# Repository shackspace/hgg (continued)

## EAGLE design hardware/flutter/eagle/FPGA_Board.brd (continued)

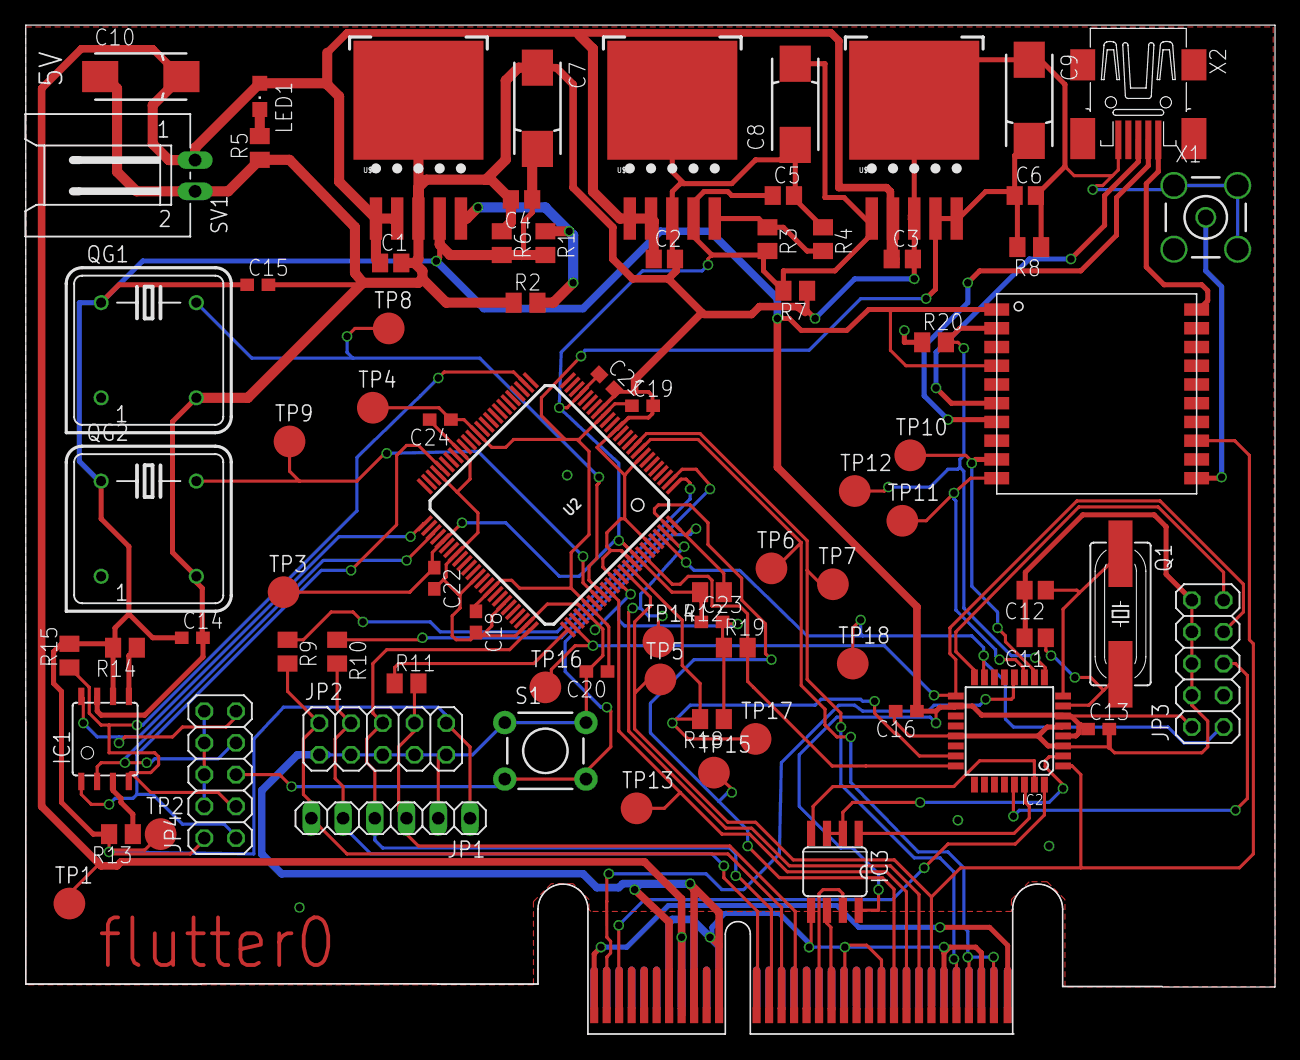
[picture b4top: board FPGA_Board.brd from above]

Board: 2 copper layers, 100.0 x 80.8 mm, 81 parts (0 on the bottom side), 53 nets.

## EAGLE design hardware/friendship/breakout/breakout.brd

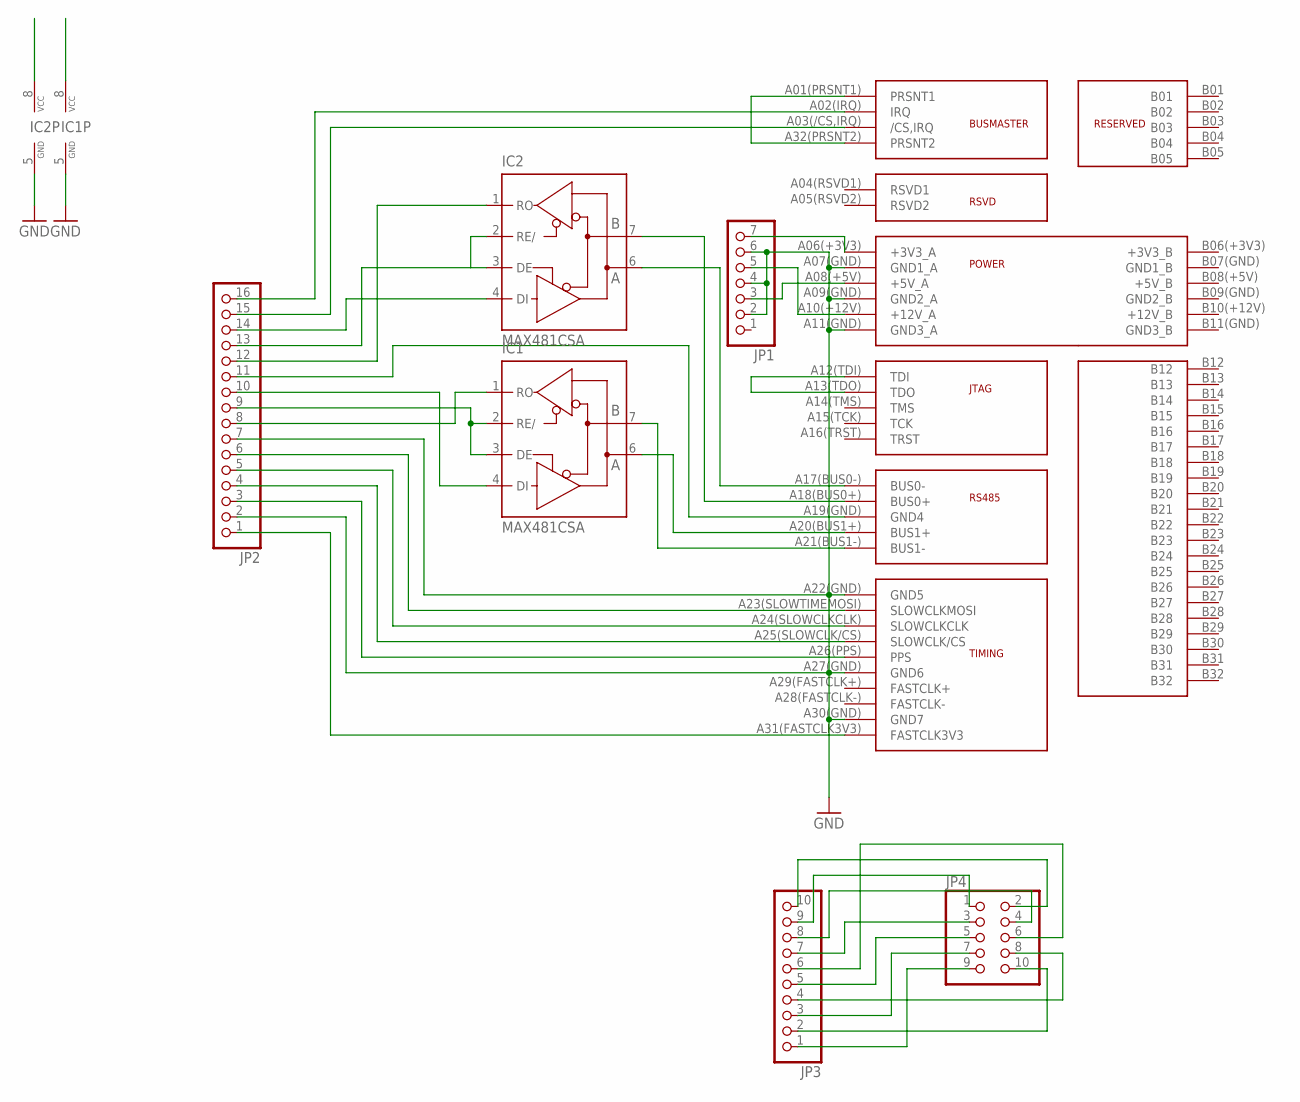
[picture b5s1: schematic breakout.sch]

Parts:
IC1, IC2: MAX481CSA; SO08
JP1: PINHD-1X7; 1X07
JP2: PINHD-1X16; 1X16
JP3: PINHD-1X10; 1X10
JP4: PINHD-2X5; 2X05
U$1: FRIENDSHIPCONNECTOR; FRIENDSHIP_EDGE_CONNECTOR

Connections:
GND: IC1.5 (GND), IC2.5 (GND), JP1.2, JP1.4, JP1.6, JP2.2, JP2.7, U$1.A07(GND) (GND1_A), U$1.A09(GND) (GND2_A), U$1.A11(GND) (GND3_A), U$1.A22(GND) (GND5), U$1.A27(GND) (GND6), U$1.A30(GND) (GND7)
unnamed: U$1.A01(PRSNT1) (PRSNT1), U$1.A32(PRSNT2) (PRSNT2)
unnamed: IC2.6 (A), U$1.A17(BUS0-) (BUS0-)
unnamed: IC2.7 (B), U$1.A18(BUS0+) (BUS0+)
unnamed: IC2.2 (RE/), IC2.3 (DE), JP2.13
unnamed: JP2.16, U$1.A02(IRQ) (IRQ)
unnamed: JP2.15, U$1.A03(/CS,IRQ) (/CS,IRQ)
unnamed: IC1.6 (A), U$1.A20(BUS1+) (BUS1+)
unnamed: IC2.4 (DI), JP2.14
unnamed: IC1.7 (B), U$1.A21(BUS1-) (BUS1-)
unnamed: JP2.11, U$1.A19(GND) (GND4)
unnamed: IC1.2 (RE/), IC1.3 (DE), JP2.9
unnamed: U$1.A12(TDI) (TDI), U$1.A13(TDO) (TDO)
unnamed: JP1.5, U$1.A10(+12V) (+12V_A)
unnamed: IC2.1 (RO), JP2.12
unnamed: IC1.1 (RO), JP2.8
unnamed: IC1.4 (DI), JP2.10
unnamed: JP2.6, U$1.A23(SLOWTIMEMOSI) (SLOWCLKMOSI)
unnamed: JP1.3, U$1.A08(+5V) (+5V_A)
unnamed: JP2.5, U$1.A24(SLOWCLKCLK) (SLOWCLKCLK)
unnamed: JP2.4, U$1.A25(SLOWCLK/CS) (SLOWCLK/CS)
unnamed: JP2.3, U$1.A26(PPS) (PPS)
unnamed: JP3.10, JP4.2
unnamed: JP2.1, U$1.A31(FASTCLK3V3) (FASTCLK3V3)
unnamed: JP3.9, JP4.1
unnamed: JP3.8, JP4.4
unnamed: JP3.7, JP4.3
unnamed: JP3.6, JP4.6
unnamed: JP3.5, JP4.5
unnamed: JP3.3, JP4.7
unnamed: JP3.4, JP4.8
unnamed: JP3.2, JP4.10
unnamed: JP3.1, JP4.9
VCC: IC1.8 (VCC), IC2.8 (VCC), JP1.7, U$1.A06(+3V3) (+3V3_A)

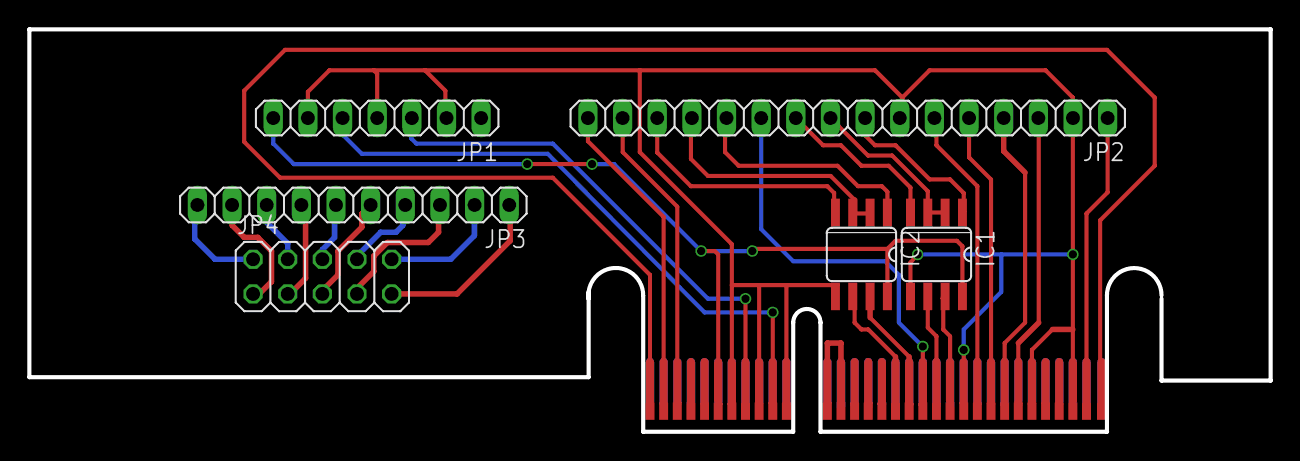
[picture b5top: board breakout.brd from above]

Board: 2 copper layers, 91.0 x 29.5 mm, 7 parts (0 on the bottom side), 34 nets.

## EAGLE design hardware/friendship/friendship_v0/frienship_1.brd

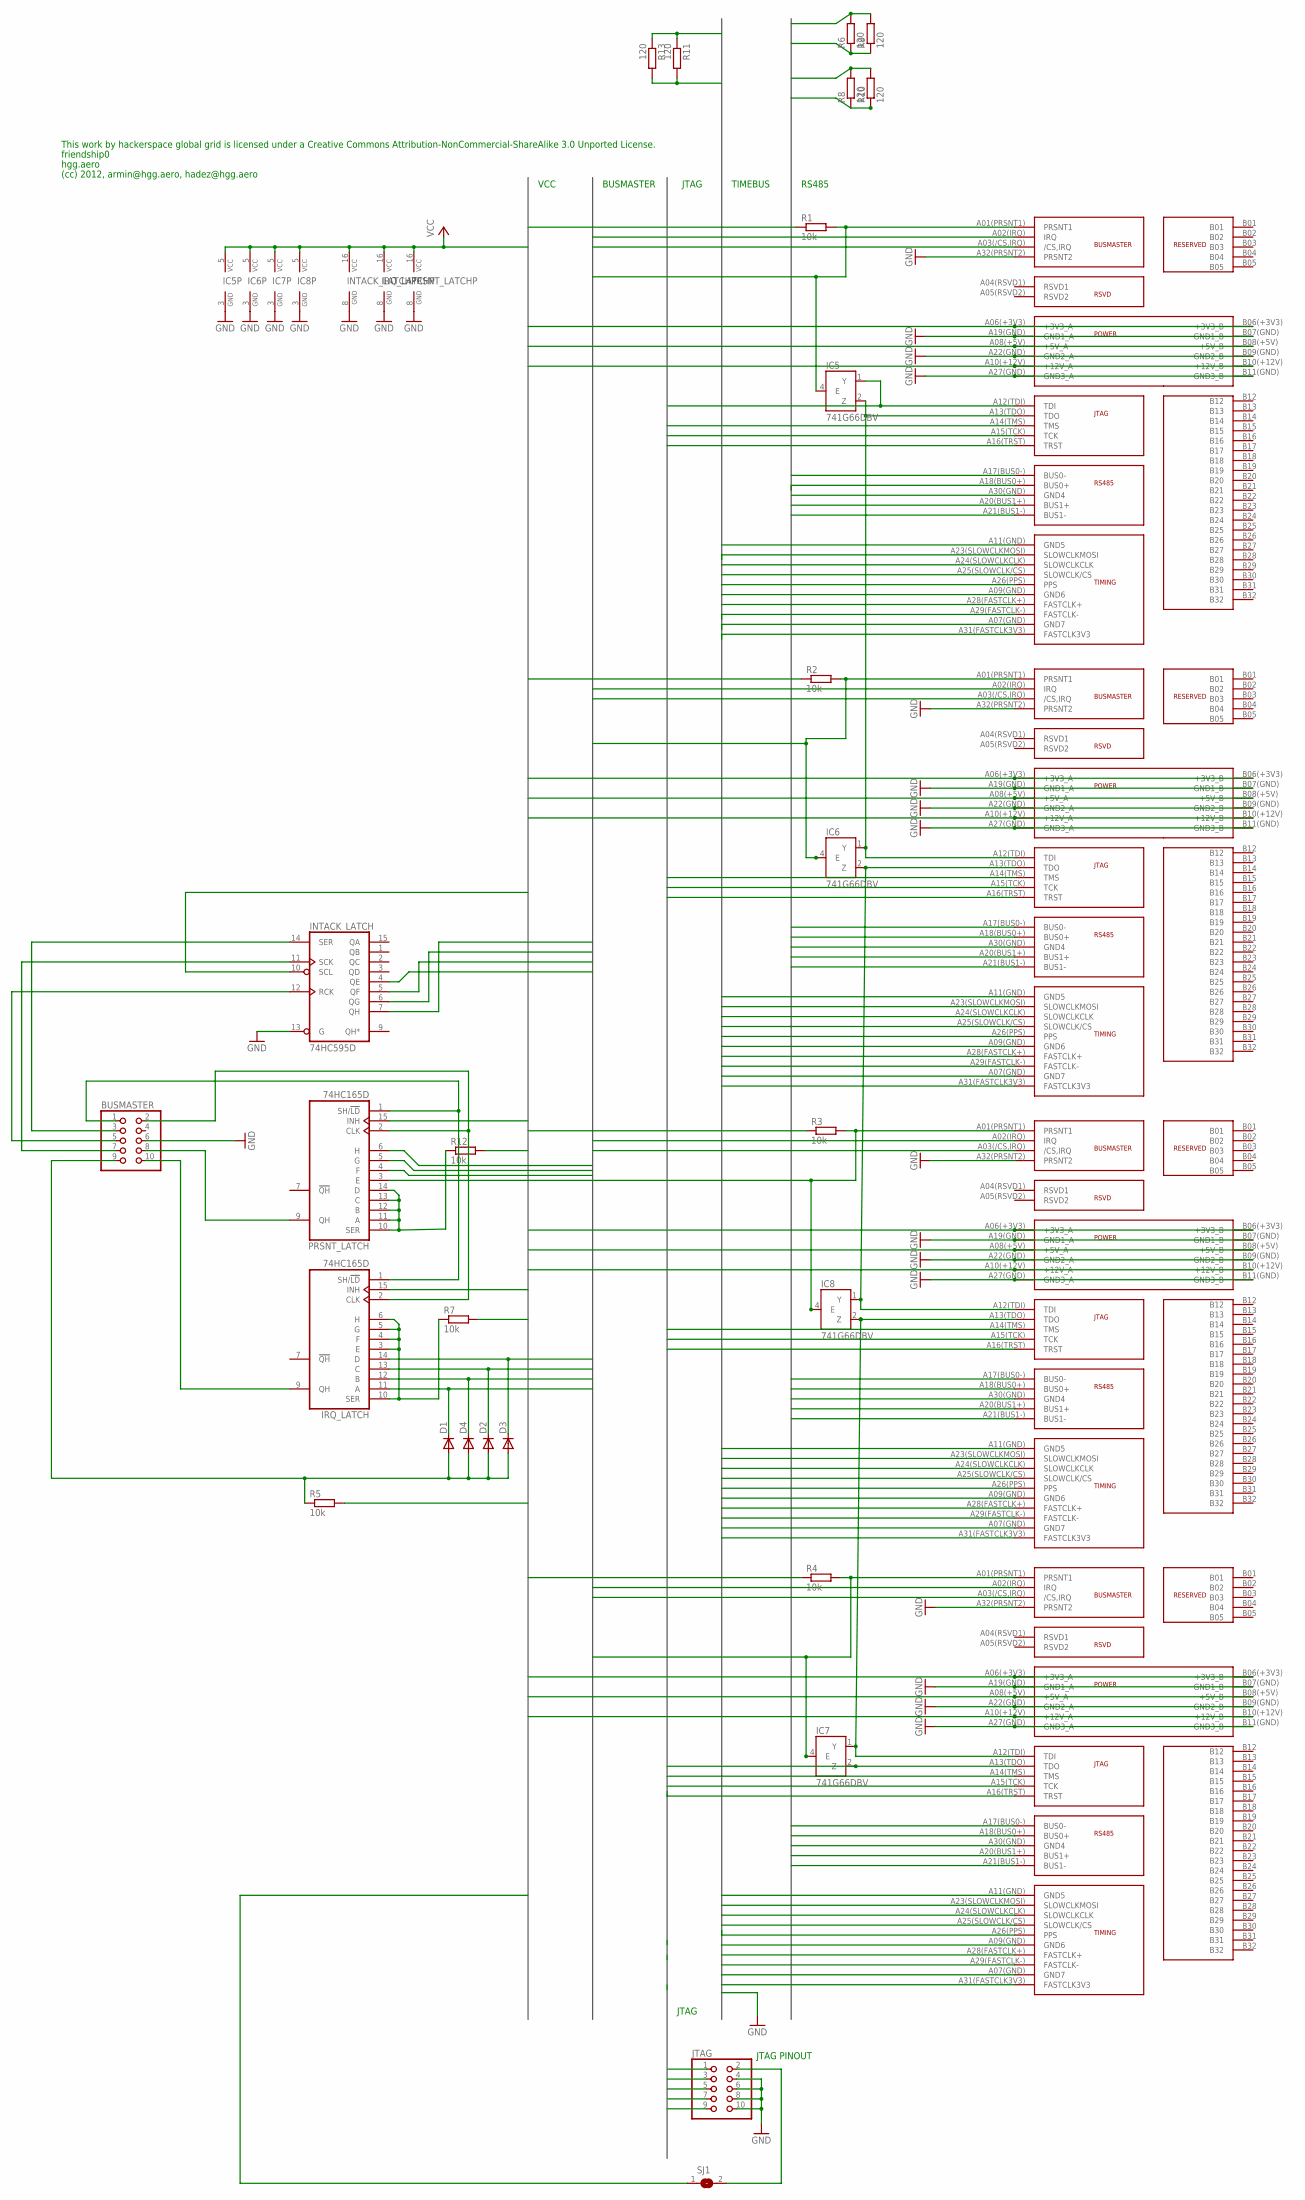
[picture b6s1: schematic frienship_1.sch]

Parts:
BUSMASTER: PINHD-2X5; 2X05
D1, D2, D3, D4: DIODE-SOD80C; SOD80C
IC5, IC6, IC7, IC8: 741G66DBV; SOT23-5
INTACK_LATCH: 74HC595D; SO16
IRQ_LATCH: 74HC165D; SO16
JTAG: PINHD-2X5; 2X05
PORT0, PORT1, PORT2, PORT3: FRIENDSHIPSLOT; FRIENDSHIP_SLOT
PRSNT_LATCH: 74HC165D; SO16
R1, R2, R3, R4, R5, R7, R12: 10k; R0603
R6, R8, R9, R10, R11, R13: 120; R0603
SJ1: SJ

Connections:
3V3: IC5.5 (VCC), IC6.5 (VCC), IC7.5 (VCC), IC8.5 (VCC), INTACK_LATCH.10 (SCL), INTACK_LATCH.16 (VCC), IRQ_LATCH.15 (INH), IRQ_LATCH.16 (VCC), PORT0.A06(+3V3) (+3V3_A), PORT0.B06(+3V3) (+3V3_B), PORT1.A06(+3V3) (+3V3_A), PORT1.B06(+3V3) (+3V3_B), PORT2.A06(+3V3) (+3V3_A), PORT2.B06(+3V3) (+3V3_B), PORT3.A06(+3V3) (+3V3_A), PORT3.B06(+3V3) (+3V3_B), PRSNT_LATCH.15 (INH), PRSNT_LATCH.16 (VCC), R1.1, R2.1, R3.1, R4.1, R5.2, R7.2, R12.2, SJ1.1
5V: PORT0.A08(+5V) (+5V_A), PORT0.B08(+5V) (+5V_B), PORT1.A08(+5V) (+5V_A), PORT1.B08(+5V) (+5V_B), PORT2.A08(+5V) (+5V_A), PORT2.B08(+5V) (+5V_B), PORT3.A08(+5V) (+5V_A), PORT3.B08(+5V) (+5V_B)
12V: PORT0.A10(+12V) (+12V_A), PORT0.B10(+12V) (+12V_B), PORT1.A10(+12V) (+12V_A), PORT1.B10(+12V) (+12V_B), PORT2.A10(+12V) (+12V_A), PORT2.B10(+12V) (+12V_B), PORT3.A10(+12V) (+12V_A), PORT3.B10(+12V) (+12V_B)
/CS: PORT0.A25(SLOWCLK/CS) (SLOWCLK/CS), PORT1.A25(SLOWCLK/CS) (SLOWCLK/CS), PORT2.A25(SLOWCLK/CS) (SLOWCLK/CS), PORT3.A25(SLOWCLK/CS) (SLOWCLK/CS)
/CS0: INTACK_LATCH.7 (QH), PORT0.A03(/CS,IRQ) (/CS,IRQ)
/CS1: INTACK_LATCH.6 (QG), PORT1.A03(/CS,IRQ) (/CS,IRQ)
/CS2: INTACK_LATCH.5 (QF), PORT2.A03(/CS,IRQ) (/CS,IRQ)
/CS3: INTACK_LATCH.4 (QE), PORT3.A03(/CS,IRQ) (/CS,IRQ)
CLK: PORT0.A24(SLOWCLKCLK) (SLOWCLKCLK), PORT1.A24(SLOWCLKCLK) (SLOWCLKCLK), PORT2.A24(SLOWCLKCLK) (SLOWCLKCLK), PORT3.A24(SLOWCLKCLK) (SLOWCLKCLK)
FASTCLK3V3: PORT0.A31(FASTCLK3V3) (FASTCLK3V3), PORT1.A31(FASTCLK3V3) (FASTCLK3V3), PORT2.A31(FASTCLK3V3) (FASTCLK3V3), PORT3.A31(FASTCLK3V3) (FASTCLK3V3)
FASTCLK+: PORT0.A28(FASTCLK+) (FASTCLK+), PORT1.A28(FASTCLK+) (FASTCLK+), PORT2.A28(FASTCLK+) (FASTCLK+), PORT3.A28(FASTCLK+) (FASTCLK+), R11.1, R13.1
FASTCLK-: PORT0.A29(FASTCLK-) (FASTCLK-), PORT1.A29(FASTCLK-) (FASTCLK-), PORT2.A29(FASTCLK-) (FASTCLK-), PORT3.A29(FASTCLK-) (FASTCLK-), R11.2, R13.2
GND: BUSMASTER.6, IC5.3 (GND), IC6.3 (GND), IC7.3 (GND), IC8.3 (GND), INTACK_LATCH.8 (GND), INTACK_LATCH.13 (G), IRQ_LATCH.8 (GND), JTAG.4, JTAG.6, JTAG.8, JTAG.10, PORT0.A07(GND) (GND7), PORT0.A09(GND) (GND6), PORT0.A11(GND) (GND5), PORT0.A19(GND) (GND1_A), PORT0.A22(GND) (GND2_A), PORT0.A27(GND) (GND3_A), PORT0.A30(GND) (GND4), PORT0.A32(PRSNT2) (PRSNT2), PORT0.B07(GND) (GND1_B), PORT0.B09(GND) (GND2_B), PORT0.B11(GND) (GND3_B), PORT1.A07(GND) (GND7), PORT1.A09(GND) (GND6), PORT1.A11(GND) (GND5), PORT1.A19(GND) (GND1_A), PORT1.A22(GND) (GND2_A), PORT1.A27(GND) (GND3_A), PORT1.A30(GND) (GND4), PORT1.A32(PRSNT2) (PRSNT2), PORT1.B07(GND) (GND1_B), PORT1.B09(GND) (GND2_B), PORT1.B11(GND) (GND3_B), PORT2.A07(GND) (GND7), PORT2.A09(GND) (GND6), PORT2.A11(GND) (GND5), PORT2.A19(GND) (GND1_A), PORT2.A22(GND) (GND2_A), PORT2.A27(GND) (GND3_A), PORT2.A30(GND) (GND4), PORT2.A32(PRSNT2) (PRSNT2), PORT2.B07(GND) (GND1_B), PORT2.B09(GND) (GND2_B), PORT2.B11(GND) (GND3_B), PORT3.A07(GND) (GND7), PORT3.A09(GND) (GND6), PORT3.A11(GND) (GND5), PORT3.A19(GND) (GND1_A), PORT3.A22(GND) (GND2_A), PORT3.A27(GND) (GND3_A), PORT3.A30(GND) (GND4), PORT3.A32(PRSNT2) (PRSNT2), PORT3.B07(GND) (GND1_B), PORT3.B09(GND) (GND2_B), PORT3.B11(GND) (GND3_B), PRSNT_LATCH.8 (GND)
IRQ0: D3.C, IRQ_LATCH.14 (D), PORT0.A02(IRQ) (IRQ)
IRQ1: D2.C, IRQ_LATCH.13 (C), PORT1.A02(IRQ) (IRQ)
IRQ2: D4.C, IRQ_LATCH.12 (B), PORT2.A02(IRQ) (IRQ)
IRQ3: D1.C, IRQ_LATCH.11 (A), PORT3.A02(IRQ) (IRQ)
MOSI: PORT0.A23(SLOWCLKMOSI) (SLOWCLKMOSI), PORT1.A23(SLOWCLKMOSI) (SLOWCLKMOSI), PORT2.A23(SLOWCLKMOSI) (SLOWCLKMOSI), PORT3.A23(SLOWCLKMOSI) (SLOWCLKMOSI)
unnamed: BUSMASTER.3, INTACK_LATCH.14 (SER)
unnamed: IC5.2 (Z), IC6.1 (Y), PORT0.A13(TDO) (TDO), PORT1.A12(TDI) (TDI)
unnamed: BUSMASTER.1, IRQ_LATCH.1 (SH/!LD), PRSNT_LATCH.1 (SH/!LD)
unnamed: BUSMASTER.7, INTACK_LATCH.11 (SCK)
unnamed: JTAG.2, SJ1.2
unnamed: IC6.2 (Z), IC8.1 (Y), PORT1.A13(TDO) (TDO), PORT2.A12(TDI) (TDI)
unnamed: IC7.1 (Y), IC8.2 (Z), PORT2.A13(TDO) (TDO), PORT3.A12(TDI) (TDI)
unnamed: IRQ_LATCH.3 (E), IRQ_LATCH.4 (F), IRQ_LATCH.5 (G), IRQ_LATCH.6 (H), IRQ_LATCH.10 (SER), R7.1
unnamed: BUSMASTER.5, INTACK_LATCH.12 (RCK)
unnamed: PRSNT_LATCH.10 (SER), PRSNT_LATCH.11 (A), PRSNT_LATCH.12 (B), PRSNT_LATCH.13 (C), PRSNT_LATCH.14 (D), R12.1
unnamed: BUSMASTER.9, D1.A, D2.A, D3.A, D4.A, R5.1
unnamed: BUSMASTER.8, PRSNT_LATCH.9 (QH)
unnamed: BUSMASTER.10, IRQ_LATCH.9 (QH)
PPS: PORT0.A26(PPS) (PPS), PORT1.A26(PPS) (PPS), PORT2.A26(PPS) (PPS), PORT3.A26(PPS) (PPS)
PRSNT0: IC5.4 (E), PORT0.A01(PRSNT1) (PRSNT1), PRSNT_LATCH.6 (H), R1.2
PRSNT1: IC6.4 (E), PORT1.A01(PRSNT1) (PRSNT1), PRSNT_LATCH.5 (G), R2.2
PRSNT2: IC8.4 (E), PORT2.A01(PRSNT1) (PRSNT1), PRSNT_LATCH.4 (F), R3.2
PRSNT3: IC7.4 (E), PORT3.A01(PRSNT1) (PRSNT1), PRSNT_LATCH.3 (E), R4.2
RX+: PORT0.A20(BUS1+) (BUS1+), PORT1.A20(BUS1+) (BUS1+), PORT2.A20(BUS1+) (BUS1+), PORT3.A20(BUS1+) (BUS1+), R8.2, R10.2
RX-: PORT0.A21(BUS1-) (BUS1-), PORT1.A21(BUS1-) (BUS1-), PORT2.A21(BUS1-) (BUS1-), PORT3.A21(BUS1-) (BUS1-), R8.1, R10.1
SHIFT: BUSMASTER.2, IRQ_LATCH.2 (CLK), PRSNT_LATCH.2 (CLK)
TCK: JTAG.7, PORT0.A15(TCK) (TCK), PORT1.A15(TCK) (TCK), PORT2.A15(TCK) (TCK), PORT3.A15(TCK) (TCK)
TDI: IC5.1 (Y), JTAG.1, PORT0.A12(TDI) (TDI)
TDO: IC7.2 (Z), JTAG.3, PORT3.A13(TDO) (TDO)
TMS: JTAG.5, PORT0.A14(TMS) (TMS), PORT1.A14(TMS) (TMS), PORT2.A14(TMS) (TMS), PORT3.A14(TMS) (TMS)
TRST: JTAG.9, PORT0.A16(TRST) (TRST), PORT1.A16(TRST) (TRST), PORT2.A16(TRST) (TRST), PORT3.A16(TRST) (TRST)
TX+: PORT0.A18(BUS0+) (BUS0+), PORT1.A18(BUS0+) (BUS0+), PORT2.A18(BUS0+) (BUS0+), PORT3.A18(BUS0+) (BUS0+), R6.2, R9.2
TX-: PORT0.A17(BUS0-) (BUS0-), PORT1.A17(BUS0-) (BUS0-), PORT2.A17(BUS0-) (BUS0-), PORT3.A17(BUS0-) (BUS0-), R6.1, R9.1

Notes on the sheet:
RS485
TIMEBUS
JTAG
BUSMASTER
VCC
JTAG PINOUT
friendship0
hgg.aero
This work by hackerspace global grid is licensed under a Creative Commons Attribution-NonCommercial-ShareAlike 3.0 Unported License.
(cc) 2012, armin@hgg.aero, hadez@hgg.aero

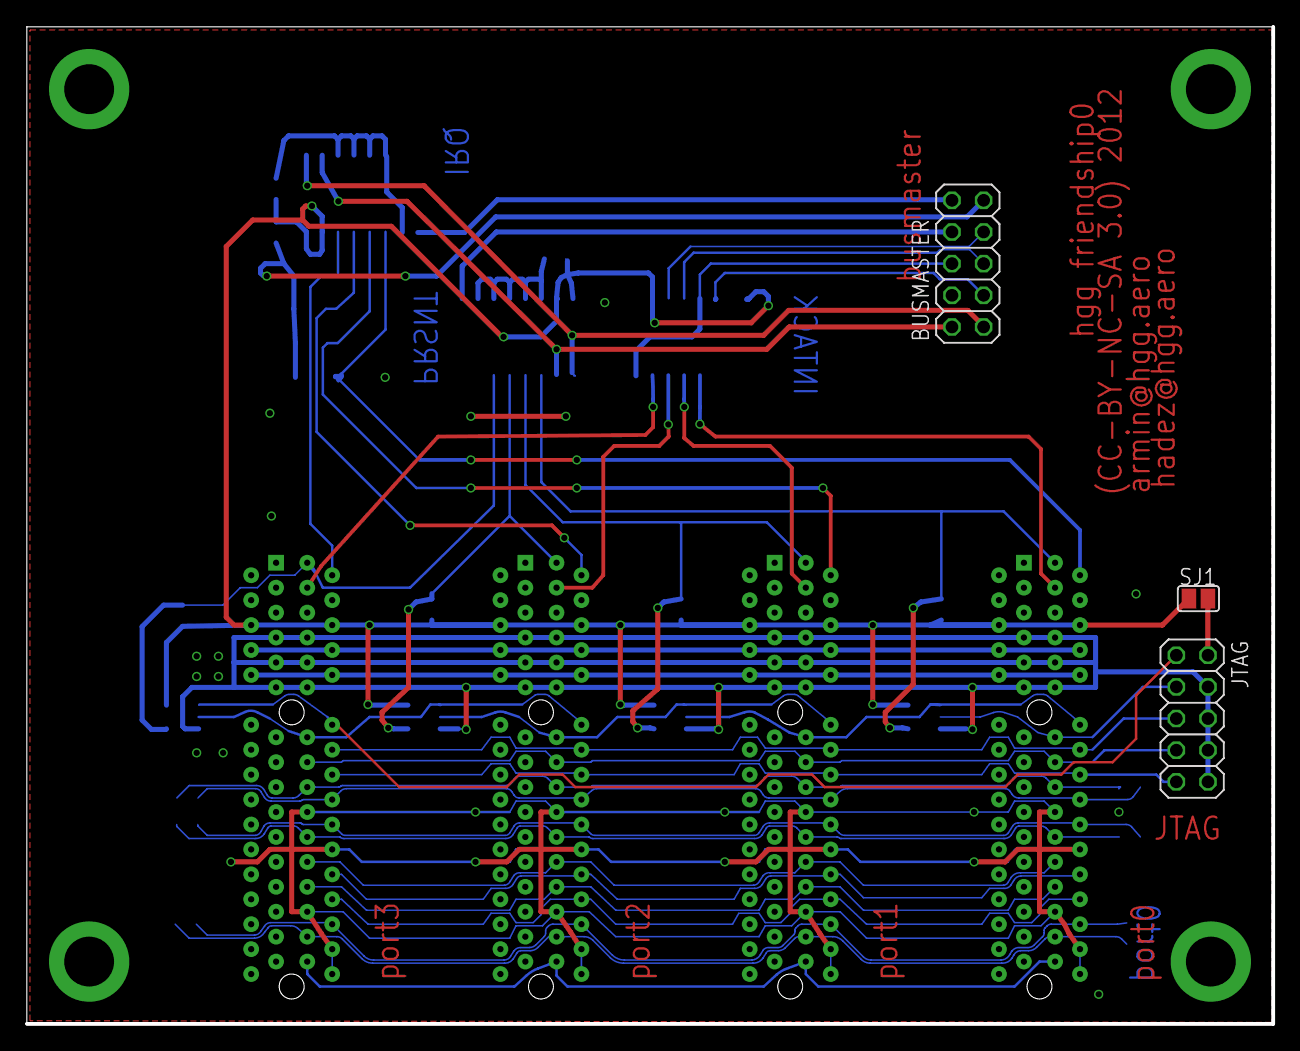
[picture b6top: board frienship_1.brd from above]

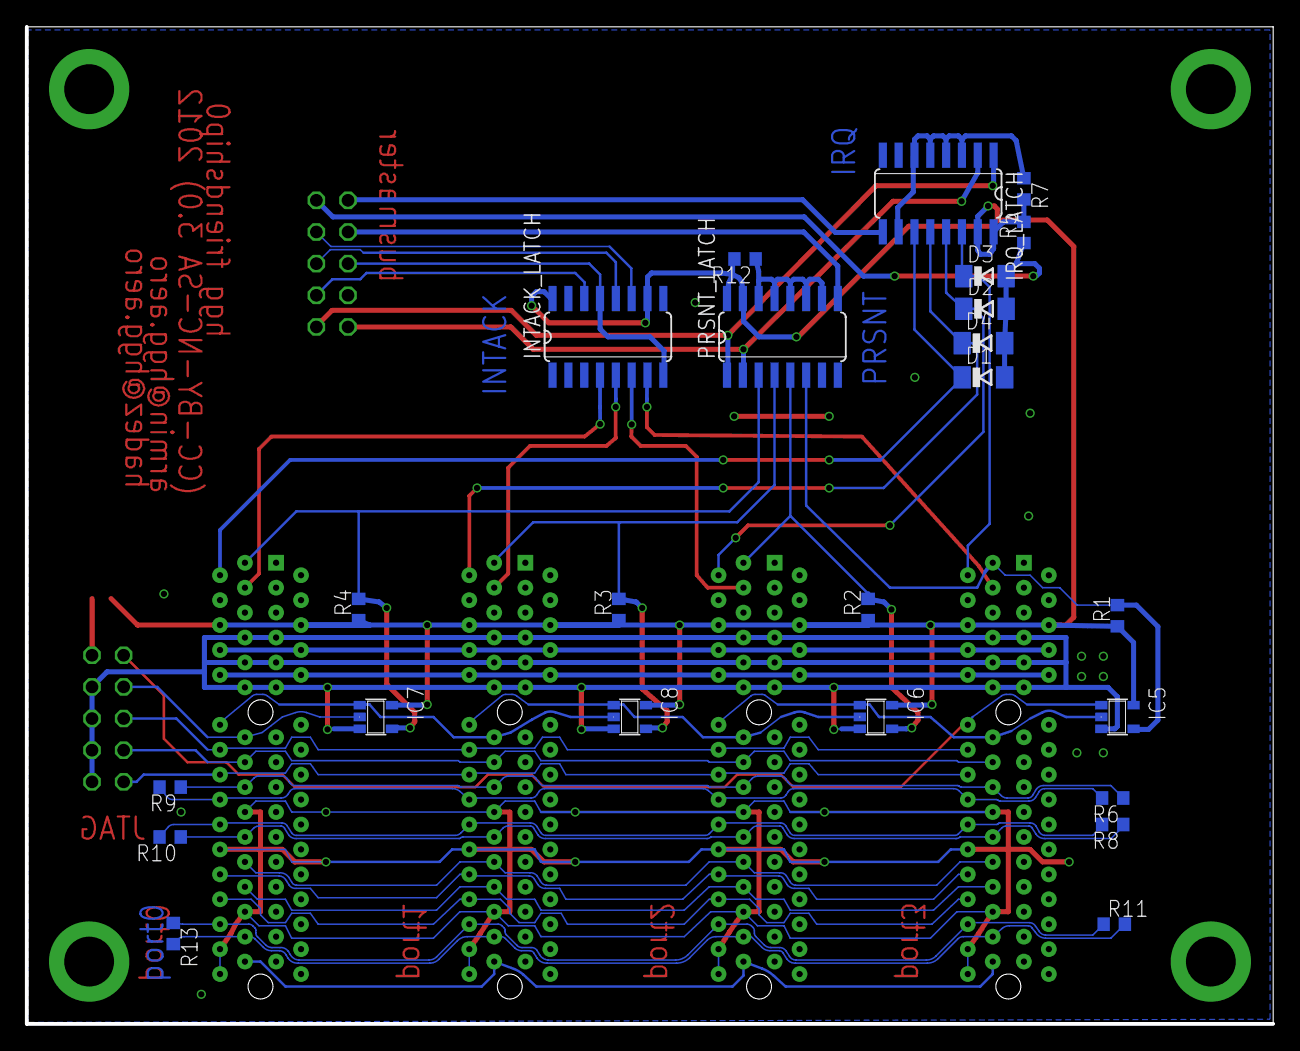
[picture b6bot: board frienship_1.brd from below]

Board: 2 copper layers, 100.0 x 80.0 mm, 31 parts (24 on the bottom side), 46 nets.
